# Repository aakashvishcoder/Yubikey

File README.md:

# Yubikey

This is my version of a YubiKey, built around the RP2040 microcontroller! It’s a compact, secure authentication device designed to generate one‑time passwords and handle cryptographic operations for two‑factor authentication. This key has several unique features and components (as listed below), and is meant to replicate the core functionality of a hardware security token.

# Features:
- Programmable LED(s)
- USBC Receptacle
- RP2040 Microcontroller
- Stores Password (through firmware)

# How to Use

The switches on the PCB can be used to boot up and reset the microcontroller, and the firmware can be modified to your liking!

# Images:

# Build of Materials (BOM)
| Item | Description | Qty | Product link | Price w/ Tax ($) | Running Total |
|------|-------------|-----|--------------|------------------|---------------|
| Capacitor | 1uF | 2 | [link](https://jlcpcb.com/partdetail/53938-CL05A105KA5NQNC/C52923) | $0.03 | $0.03 |
| Capacitor | 0.1uF | 4 | [link](https://jlcpcb.com/partdetail/1877-CL05B104KO5NNNC/C1525) | $0.07 | $0.10 |
| Capacitor | 10uF | 1 | [link](https://jlcpcb.com/partdetail/2043-CL10A106MQ8NNNC/C1691) | $0.09 | $0.19 |
| Capacitor | 15pF | 2 | [link](https://jlcpcb.com/partdetail/1914-0402CG150J500NT/C1547) | $0.01 | $0.20 |
| Resistor | 5.1k | 2 | [link](https://jlcpcb.com/partdetail/26648-0402WGF5101TCE/C25905) | $0.01 | $0.21 |
| Resistor | 470 | 1 | [link](https://jlcpcb.com/partdetail/UNIROYAL-0402WGF4700TCE/C25130) | $0.01 | $0.22 |
| Resistor | 4.7k | 2 | [link](https://jlcpcb.com/partdetail/UNIROYAL-0402WGF4701TCE/C25867) | $0.01 | $0.23 |
| Resistor | 10k | 1 | [link](https://jlcpcb.com/partdetail/UNIROYAL-0402WGF1002TCE/C25744) | $0.01 | $0.24 |
| Resistor | 27 | 2 | [link](https://jlcpcb.com/partdetail/UNIROYAL-0402WGF270JTCE/C25100) | $0.01 | $0.25 |
| Resistor | 1k | 1 | [link](https://jlcpcb.com/partdetail/UNIROYAL-0402WGF1001TCE/C11702) | $0.01 | $0.26 |
| SW_Push | Tactile Button | 2 | [link](https://jlcpcb.com/partdetail/XKBConnectivity-TS-1187A-B-A-B/C318884) | $0.42 | $0.68 |
| LED | Indicator LED 0402 | 1 | [link](https://jlcpcb.com/partdetail/Honglitronic-HL-LED0402R/C2290) | $0.02 | $0.70 |
| WS2812B | RGB LED | 1 | [link](https://jlcpcb.com/partdetail/Worldsemi-WS2812B_BT/C2761795) | $0.20 | $0.90 |
| RP2040 | Microcontroller | 1 | [link](https://jlcpcb.com/partdetail/RaspberryPi-RP2040/C2040) | $4.58 | $5.48 |
| USB Receptacle | USB-C 16P | 1 | [link](https://jlcpcb.com/partdetail/Korean_HropartsElec-TYPE_C_31_M12/C165948) | $0.85 | $6.33 |
| ATECC608A | Secure Element | 1 | [link](https://jlcpcb.com/partdetail/MicrochipTech-ATECC608ASSHDA/C148118) | $1.97 | $8.30 |
| W25Q128JVS | Flash Storage | 1 | [link](https://jlcpcb.com/partdetail/WinbondElec-W25Q128JVSIQ/C97521) | $2.67 | $10.97 |
| Crystal | 12MHz 3225 | 1 | [link](https://jlcpcb.com/partdetail/YXC_CrystalOscillators-X322512MSB4SI/C9002) | $0.32 | $11.29 |
| Conn_01x03 | Pin Header 1x3 | 1 | [link](https://jlcpcb.com/partdetail/BOOMELE-BM03B-SRSS-TB/C42431804) | $0.05 | $11.34 |
| Conn_01x20 | 1x20 Pin Headers | 2 | [link](https://jlcpcb.com/partdetail/BOOMELE-BM20B-SRSS-TB/C42431804) | $0.17 | $11.51 |
| Yubikey PCBA | PCBA board assembly | 1 | [link](https://cart.jlcpcb.com/) | $43.94 | $55.45 |

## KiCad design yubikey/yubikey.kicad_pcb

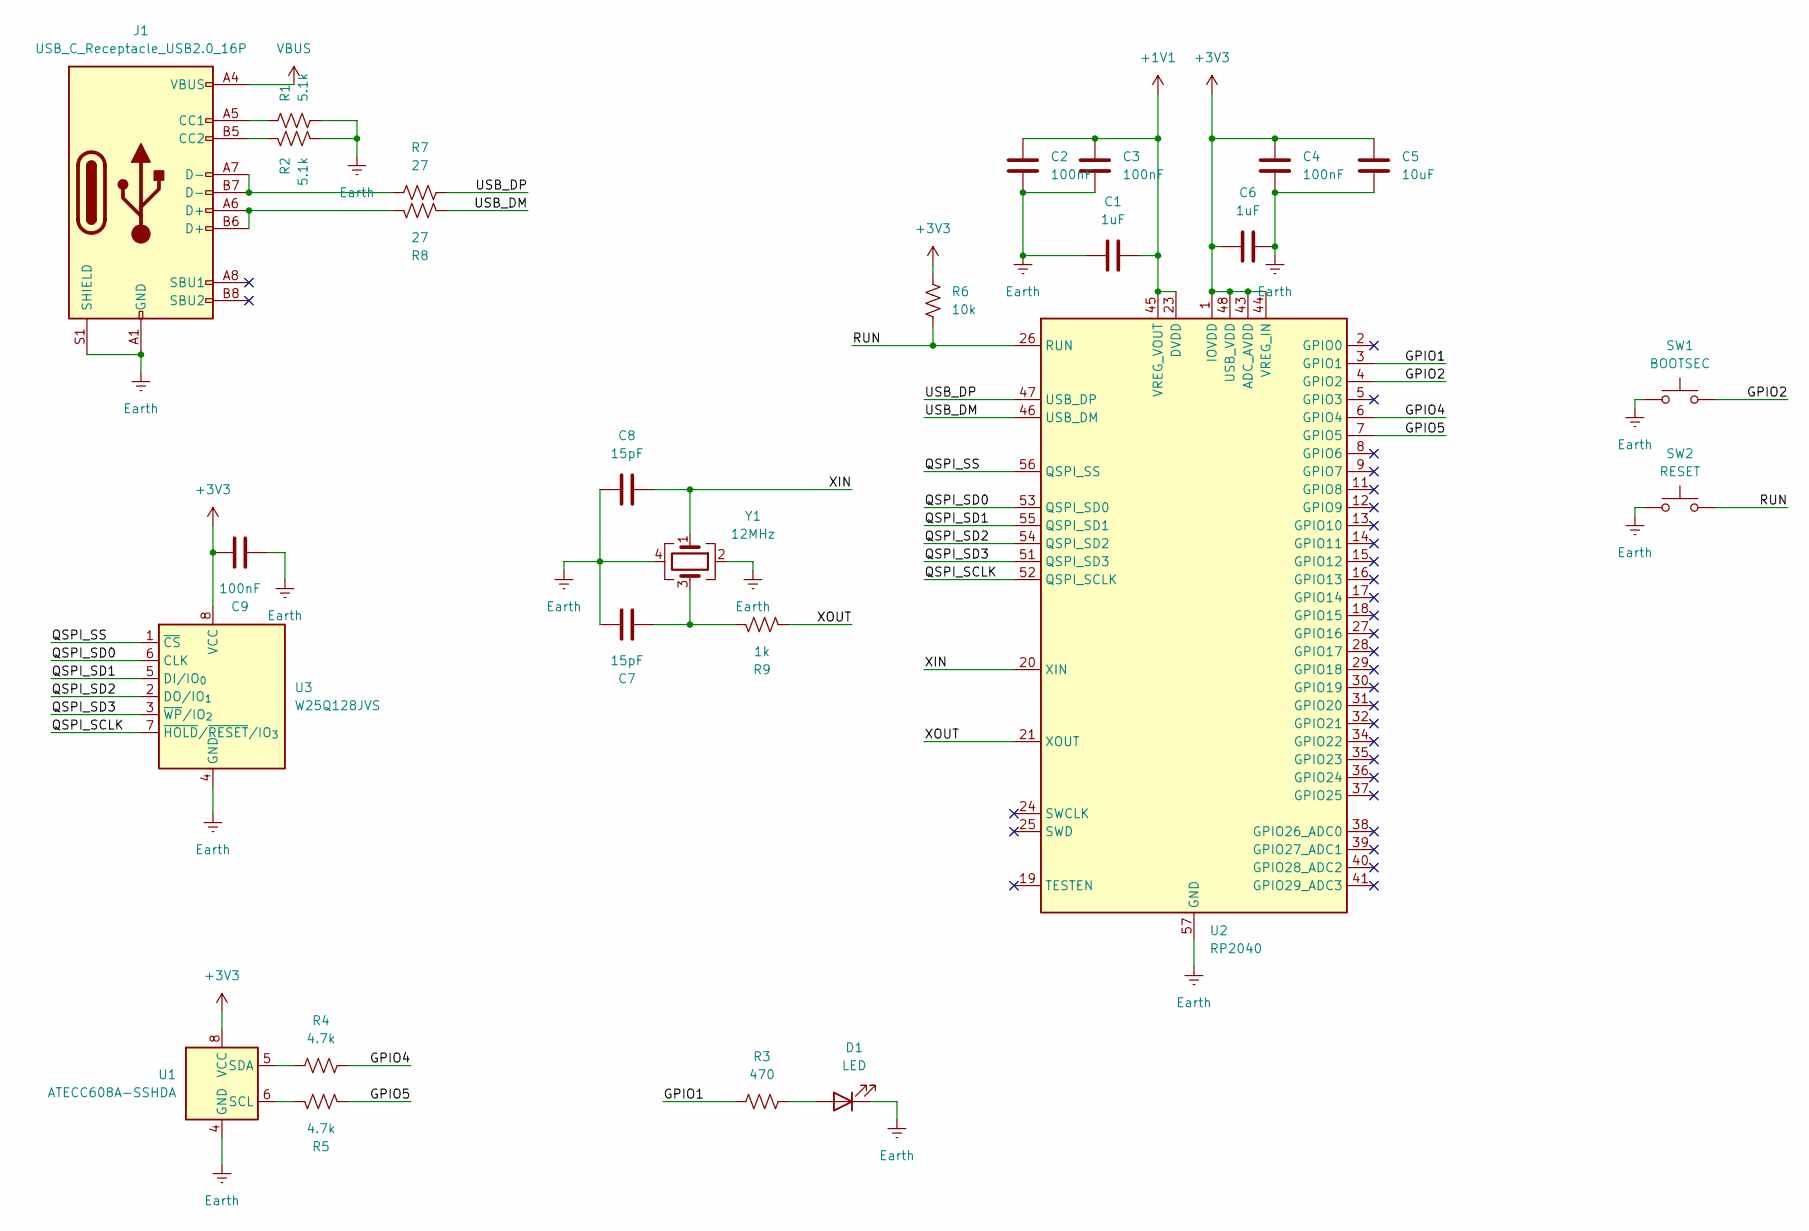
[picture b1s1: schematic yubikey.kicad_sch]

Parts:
C1, C6: 1uF; C_0402_1005Metric
C2, C3, C4, C9: 100nF; C_0402_1005Metric
C5: 10uF; C_0402_1005Metric
C7, C8: 15pF; C_0402_1005Metric
D1: LED; C_0402_1005Metric
J1: USB_C_Receptacle_USB2.0_16P; USB_C_Receptacle_GCT_USB4105-xx-A_16P_TopMnt_Horizontal
R1, R2: 5.1k; L_0402_1005Metric
R3: 470; L_0402_1005Metric
R4, R5: 4.7k; L_0402_1005Metric
R6: 10k; L_0402_1005Metric
R7, R8: 27; L_0402_1005Metric
R9: 1k; L_0402_1005Metric
SW1: BOOTSEC; SW_Tactile_SPST_NO_Straight_CK_PTS636Sx25SMTRLFS
SW2: RESET; SW_Tactile_SPST_NO_Straight_CK_PTS636Sx25SMTRLFS
U1: ATECC608A-SSHDA; SOIC-8_3.9x4.9mm_P1.27mm
U2: RP2040; QFN-56-1EP_7x7mm_P0.4mm_EP3.2x3.2mm
U3: W25Q128JVS; SOIC-8_5.3x5.3mm_P1.27mm
Y1: 12MHz; Crystal_SMD_Abracon_ABM8G-4Pin_3.2x2.5mm

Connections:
+1V1: C1.2, C2.2, C3.2, U2.23 (DVDD), U2.45 (VREG_VOUT), U2.50 (DVDD)
+3V3: C4.2, C5.2, C6.2, C9.1, R6.1, U1.8 (VCC), U2.1 (IOVDD), U2.10 (IOVDD), U2.22 (IOVDD), U2.33 (IOVDD), U2.42 (IOVDD), U2.43 (ADC_AVDD), U2.44 (VREG_IN), U2.48 (USB_VDD), U2.49 (IOVDD), U3.8 (VCC)
/GPIO1: R3.1, U2.3 (GPIO1)
/GPIO2: SW1.2, U2.4 (GPIO2)
/GPIO4: R4.1, U2.6 (GPIO4)
/GPIO5: R5.1, U2.7 (GPIO5)
/QSPI_SCLK: U2.52 (QSPI_SCLK), U3.7 (~HOLD/~RESET/IO_{3})
/QSPI_SD0: U2.53 (QSPI_SD0), U3.6 (CLK)
/QSPI_SD1: U2.55 (QSPI_SD1), U3.5 (DI/IO_{0})
/QSPI_SD2: U2.54 (QSPI_SD2), U3.2 (DO/IO_{1})
/QSPI_SD3: U2.51 (QSPI_SD3), U3.3 (~WP/IO_{2})
/QSPI_SS: U2.56 (QSPI_SS), U3.1 (~CS)
/RUN: R6.2, SW2.2, U2.26 (RUN)
/USB_DM: R8.2, U2.46 (USB_DM)
/USB_DP: R7.2, U2.47 (USB_DP)
/XIN: C8.2, U2.20 (XIN), Y1.1
/XOUT: R9.2, U2.21 (XOUT)
Earth: C1.1, C2.1, C3.1, C4.1, C5.1, C6.1, C7.1, C8.1, C9.2, D1.1 (K), J1.A1 (GND), J1.A12 (GND), J1.B1 (GND), J1.B12 (GND), J1.S1 (SHIELD), R1.2, R2.2, SW1.1, SW2.1, U1.4 (GND), U2.57 (GND), U3.4 (GND), Y1.2, Y1.4
unnamed: C7.2, R9.1, Y1.3
unnamed: D1.2 (A), R3.2
unnamed: J1.A5 (CC1), R1.1
unnamed: J1.B5 (CC2), R2.1
unnamed: J1.A6 (D+), J1.B6 (D+), R8.1
unnamed: J1.A7 (D-), J1.B7 (D-), R7.1
unnamed: R5.2, U1.6 (SCL)
unnamed: R4.2, U1.5 (SDA)
VBUS: J1.A4 (VBUS), J1.A9 (VBUS), J1.B4 (VBUS), J1.B9 (VBUS)

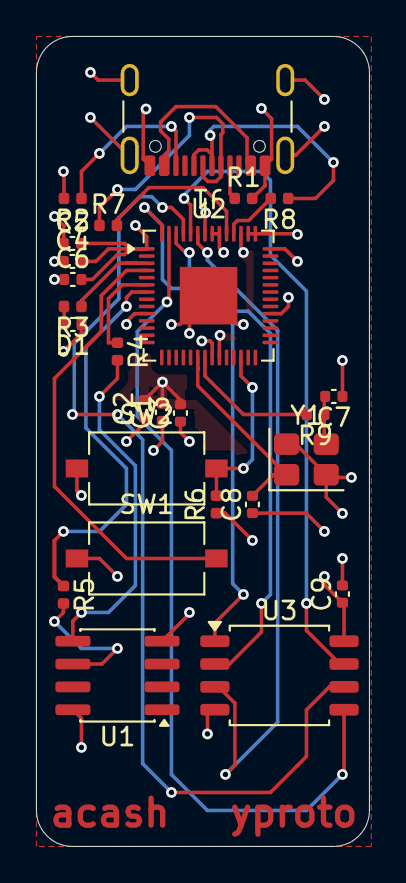
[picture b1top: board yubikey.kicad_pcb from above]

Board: 4 copper layers, 18.5 x 45.0 mm, 26 parts (0 on the bottom side), 27 nets.

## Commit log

2025-11-29 completed yubikey
2025-11-29 Add initial README for Yubikey project
2025-11-29 added some more pictures to the pcb
2025-11-29 firmware complete!
2025-11-30 Enhance README with features and images
    Added features and images sections to README.
2025-12-01 quick few updates
2025-12-01 Update BOM with pricing information
    Added price and total columns to the BOM section.
2025-12-03 fixed gitignore, made gerber and production files, finished the bom
2025-12-03 fixed bom
2025-12-03 forgot to comit
2025-12-03 Revise BOM with detailed item information
    Updated the Bill of Materials (BOM) section with item descriptions, quantities, product links, and prices.
2025-12-03 moved some files arounjd
2025-12-03 Enhance README introduction with project details
    Expanded the introduction to provide more details about the YubiKey project and its features.
2025-12-04 fixed some issues with pcb
